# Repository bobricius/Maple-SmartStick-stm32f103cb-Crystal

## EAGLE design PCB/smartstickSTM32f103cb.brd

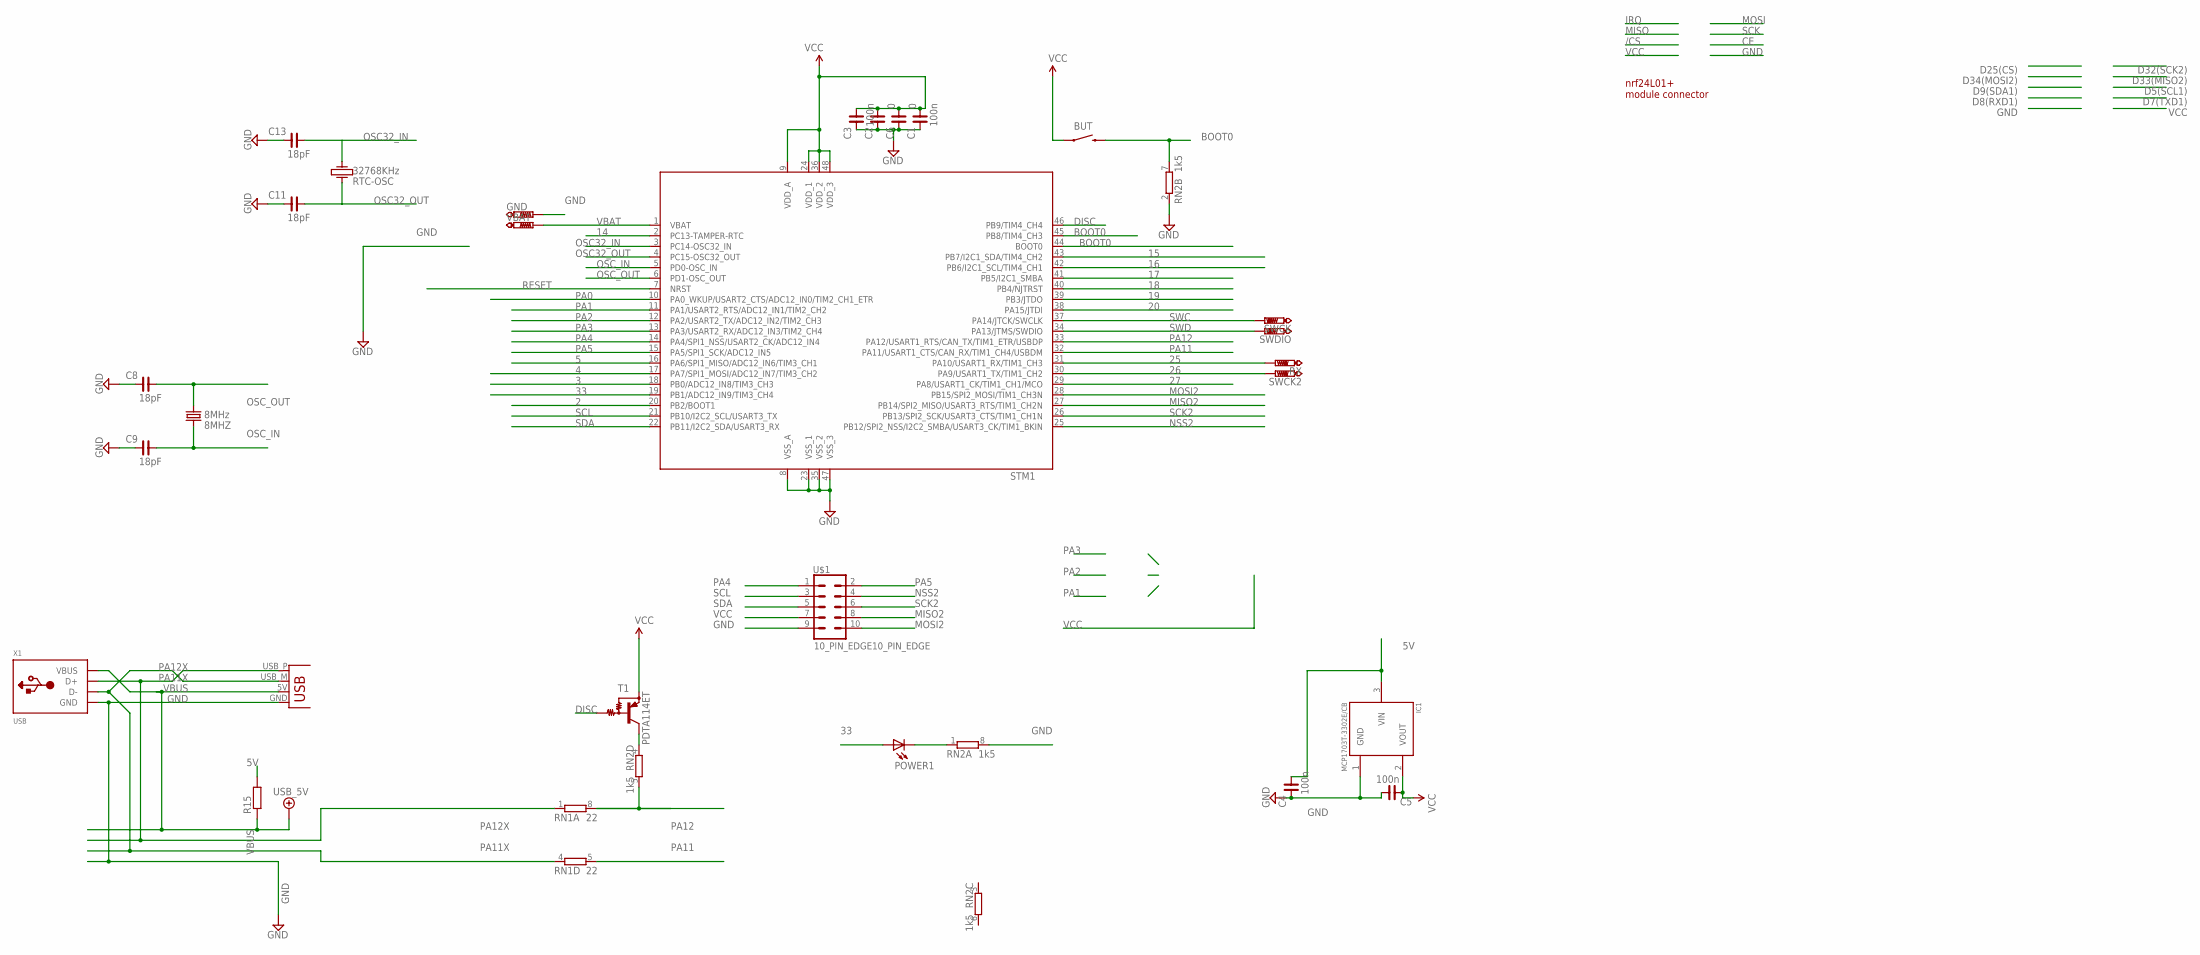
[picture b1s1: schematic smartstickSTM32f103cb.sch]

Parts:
8MHZ: 8MHz; HC49US
BUT: SWITCH-MOMENTARY-2-SMD-1101NE; TACTILE-SWITCH-1101NE
C1, C3, C4, C5: 100n; C0603
C2, C6: 0; C0603
C8, C9, C11, C13: 18pF; C0603
GND: PTR1TP20SQ; TP20SQ
IC1: MCP1703T-3302E/CB; SOT23
POWER1: Power; LED-0603
R15: R-EU_R0603; R0603
RN1: 22; 0603-ARC
RN2: 1k5; 0603-ARC
RTC-OSC: 32768KHz; KX-327LT
RX: PTR1TP10R; TP10R
STM1: STM32F103CB; LQFP48
SWCK: PTR1TP16R; TP16R
SWCK2: PTR1TP10R; TP10R
SWDIO: PTR1TP16R; TP16R
T1: PDTA114ET; ES_SOT23-3
U$1: 10_PIN_EDGE10_PIN_EDGE; 10_PIN_EDGE
VBAT: PTR1TP19R; TP19R
X1: USB; MOLEX-48037-1000
X3: USBPCB; USB-A-PCB

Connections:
2: STM1.20 (PB2/BOOT1)
3: STM1.18 (PB0/ADC12_IN8/TIM3_CH3)
4: STM1.17 (PA7/SPI1_MOSI/ADC12_IN7/TIM3_CH2)
5: STM1.16 (PA6/SPI1_MISO/ADC12_IN6/TIM3_CH1)
5V: C4.1, IC1.3 (VIN), R15.2
14: STM1.2 (PC13-TAMPER-RTC)
15: STM1.43 (PB7/I2C1_SDA/TIM4_CH2)
16: STM1.42 (PB6/I2C1_SCL/TIM4_CH1)
17: STM1.41 (PB5/I2C1_SMBA)
18: STM1.40 (PB4/NJTRST)
19: STM1.39 (PB3/JTDO)
20: STM1.38 (PA15/JTDI)
25: RX.TP, STM1.31 (PA10/USART1_RX/TIM1_CH3)
26: STM1.30 (PA9/USART1_TX/TIM1_CH2), SWCK2.TP
27: STM1.29 (PA8/USART1_CK/TIM1_CH1/MCO)
33: POWER1.A, STM1.19 (PB1/ADC12_IN9/TIM3_CH4)
BOOT0: BUT.P$2 (2), RN2.7 (2), STM1.44 (BOOT0), STM1.45 (PB8/TIM4_CH3)
DISC: STM1.46 (PB9/TIM4_CH4), T1.1 (B)
GND: C1.2, C2.2, C3.2, C4.2, C5.1, C6.2, C8.2, C9.2, C11.2, C13.2, GND.TP, IC1.1 (GND), RN2.2 (1), RN2.8 (2), STM1.8 (VSS_A), STM1.23 (VSS_1), STM1.35 (VSS_2), STM1.47 (VSS_3), U$1.9, X1.4 (GND), X3.GND
MISO2: STM1.27 (PB14/SPI2_MISO/USART3_RTS/TIM1_CH2N), U$1.8
MOSI2: STM1.28 (PB15/SPI2_MOSI/TIM1_CH3N), U$1.10
unnamed: POWER1.C, RN2.1
unnamed: RN2.4 (1), T1.3 (C)
NSS2: STM1.25 (PB12/SPI2_NSS/I2C2_SMBA/USART3_CK/TIM1_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), U$1.4
OSC32_IN: C13.1, RTC-OSC.1, STM1.3 (PC14-OSC32_IN)
OSC32_OUT: C11.1, RTC-OSC.4, STM1.4 (PC15-OSC32_OUT)
OSC_IN: 8MHZ.2, C9.1, STM1.5 (PD0-OSC_IN)
OSC_OUT: 8MHZ.1, C8.1, STM1.6 (PD1-OSC_OUT)
PA0: STM1.10 (PA0_WKUP/USART2_CTS/ADC12_IN0/TIM2_CH1_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)
PA1: STM1.11 (PA1/USART2_RTS/ADC12_IN1/TIM2_CH2)
PA2: STM1.12 (PA2/USART2_TX/ADC12_IN2/TIM2_CH3)
PA3: STM1.13 (PA3/USART2_RX/ADC12_IN3/TIM2_CH4)
PA4: STM1.14 (PA4/SPI1_NSS/USART2_CK/ADC12_IN4), U$1.1
PA5: STM1.15 (PA5/SPI1_SCK/ADC12_IN5), U$1.2
PA11: RN1.5 (2), STM1.32 (PA11/USART1_CTS/CAN_RX/TIM1_CH4/USBDM)
PA11X: RN1.4 (1), X1.2 (D-), X3.USB_M (D-)
PA12: RN1.8 (2), RN2.5 (2), STM1.33 (PA12/USART1_RTS/CAN_TX/TIM1_ETR/USBDP)
PA12X: RN1.1, X1.3 (D+), X3.USB_P (D+)
RESET: STM1.7 (NRST)
SCK2: STM1.26 (PB13/SPI2_SCK/USART3_CTS/TIM1_CH1N), U$1.6
SCL: STM1.21 (PB10/I2C2_SCL/USART3_TX), U$1.3
SDA: STM1.22 (PB11/I2C2_SDA/USART3_RX), U$1.5
SWC: STM1.37 (PA14/JTCK/SWCLK), SWCK.TP
SWD: STM1.34 (PA13/JTMS/SWDIO), SWDIO.TP
VBAT: STM1.1 (VBAT), VBAT.TP
VBUS: R15.1, X1.1 (VBUS), X3.5V (VBUS)
VCC: BUT.P$1 (1), C1.1, C2.1, C3.1, C5.2, C6.1, IC1.2 (VOUT), STM1.9 (VDD_A), STM1.24 (VDD_1), STM1.36 (VDD_2), STM1.48 (VDD_3), T1.2 (E), U$1.7

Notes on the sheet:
BOOT0
nrf24L01+ module connector

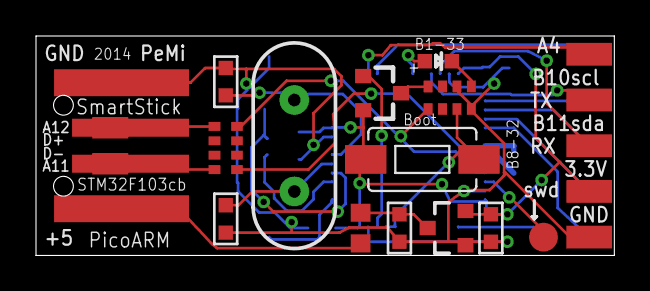
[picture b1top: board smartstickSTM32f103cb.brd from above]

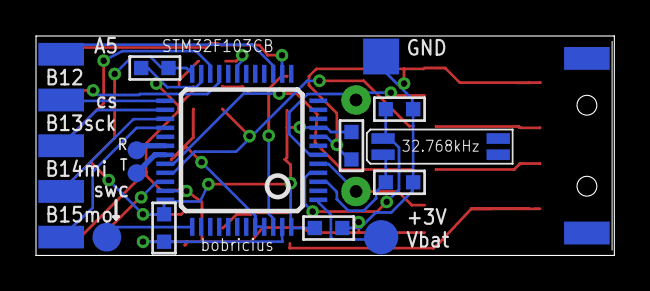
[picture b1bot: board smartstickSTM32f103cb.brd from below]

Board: 2 copper layers, 32.1 x 12.2 mm, 29 parts (13 on the bottom side), 30 nets.

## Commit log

2014-11-12 :lollipop: Added .gitattributes & .gitignore files
2014-11-12 first upload
